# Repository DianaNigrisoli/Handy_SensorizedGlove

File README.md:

# Handy_SensorizedGlove
A wireless sensorized glove for ASL fingerspelling gesture recognition. 
### Course
Electronic Technologies and Biosensor Laboratories

### Developers 
- Arianna De Vecchi <br> arianna.devecchi@mail.polimi.it
- Ilaria Crupi <br> ilaria.crupi@mail.polimi.it
- Diana Nigrisoli <br> diana.nigrisoli@mail.polimi.it

### Setup
* In the command prompt execute:
    ```console
    git clone https://github.com/DianaNigrisoli/Handy_SensorizedGlove.git
    
### Development 
You can find all the scripts and designs in the following folders: 
* Hardware: EAGLE design of the PCB
* Firmware: PSoC Creator code
* Software: Python software for GUI development and Machine Learning classification 
* Box_Solidworks: SOLIDWORKS Part Document of the 3D printed box

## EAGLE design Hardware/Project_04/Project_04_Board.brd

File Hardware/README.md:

# Hardware

## Contents 
In "Project_04" folder: 

| File | Description |
|------|-------------|
| `Project_04_Schematic.sch` | Schematic |
| `Project_04_Board.brd` | Board |
| `Project_04_ToPrint.pdf` | PCB Design PDF file 1:1 scaled |
| `sparkfun.dru` | Design rules | 
| `README.md` | This README file. |

## Tools 

Both Schematic and Board Design were implemented using the 9.6.2 version of EAGLE software. 

## Detailed files description 
### Schematic 
#### List of schematic components 
| Name | Description | On PCB |
| --------- | ----------- | ------ |
| J1 | Plated through-hole 7 pin connector | Generic 0.1 inch spaced male headers connected to flex sensors and force-sensing resistors |
| J2 | Plated through-hole 7 pin connector | Generic 0.1 inch spaced male headers connected to 3.3V supply voltage | 
| J3.1 - PSOC | Plated through-hole 7 pin connector | Generic 0.1 inch spaced female headers connected to PSOC pins from 0.0 to 0.7 |
| J3.2 - PSOC | Plated through-hole 2 pin connector | Generic 0.1 inch spaced female headers connected to PSOC pins 12.0 (SCL) and 12.1 (SDA) |
| J3.3 - PSOC | Plated through-hole 4 pin connector | Generic 0.1 inch spaced female headers connected to PSOC pins 12.6 (RX), 12.7 (TX), 2.7 and 2.6 |
| J3.4 - PSOC | Plated through-hole 2 pin connector | Generic 0.1 inch spaced female headers connected to PSOC pins VDDIO and GND |
| J3 - LED | Plated through-hole 2 pin connector | Generic 0.1 inch spaced male headers connected to yellow LED |
| J4 - BATTERY | Plated through-hole 2 pin connector | Generic 0.1 inch spaced female headers connected to 4.5V external battery and external switch |
| J5 - BT | Plated through-hole 6 pin connector | Generic 0.1 inch spaced male headers connected to HC-05 Bluetooth module |
| J6 - ACC | Plated through-hole 6 pin connector | Generic 0.1 inch spaced male headers connected to LIS3DH Accelerometer |
| J7 - LDO | Plated through-hole 3 pin connector | Generic 0.1 inch spaced male headers connected to 3.3V voltage regulator |

### Board Design
55.88mm x 73.66 mm single layer board design according to the design rules in the sparkfun.dru file.

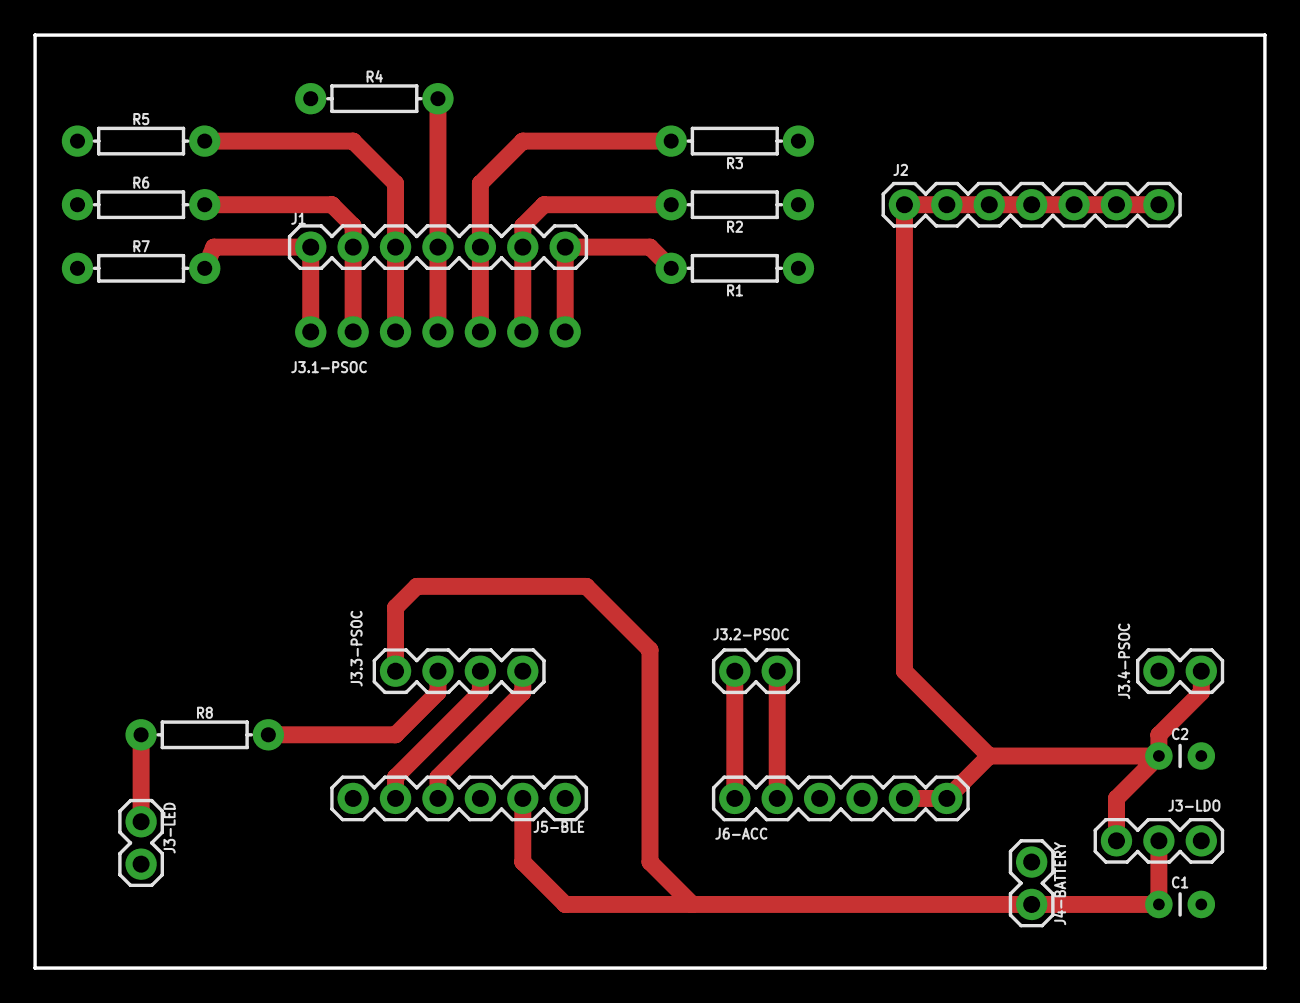
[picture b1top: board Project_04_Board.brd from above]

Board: 2 copper layers, 73.7 x 55.9 mm, 21 parts (1 on the bottom side), 15 nets.

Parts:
C1, C2: 1uF; CAP-PTH-2.54
J1, J2, J3.1-PSOC: 1X07
J3-LDO: 1X03
J3-LED, J3.2-PSOC, J3.4-PSOC, J4-BATTERY: 1X02
J3.3-PSOC: 1X04
J5-BLE, J6-ACC: 1X06
R1, R2, R3, R4, R5: 27K; AXIAL-0.3
R6, R7: 10K; AXIAL-0.3
R8: 330; AXIAL-0.3

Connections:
3.3V: C2.1, J2.1, J2.2, J2.3, J2.4, J2.5, J2.6, J2.7, J3-LDO.3, J3.4-PSOC.2, J6-ACC.5, J6-ACC.6
4.5V: C1.1, J3-LDO.2, J3.3-PSOC.1, J4-BATTERY.2, J5-BLE.2
GND: C1.2, C2.2, J3-LDO.1, J3-LED.2, J3.4-PSOC.1, J4-BATTERY.1, J5-BLE.3, J6-ACC.3, J6-ACC.4, R1.P$1, R2.P$1, R3.P$1, R4.P$1, R5.P$1, R6.P$1, R7.P$1
R1: J1.7, J3.1-PSOC.1, R1.P$2
R2: J1.6, J3.1-PSOC.2, R2.P$2
R3: J1.5, J3.1-PSOC.3, R3.P$2
R4: J1.4, J3.1-PSOC.4, R4.P$2
R5: J1.3, J3.1-PSOC.5, R5.P$2
R6: J1.2, J3.1-PSOC.6, R6.P$2
R7: J1.1, J3.1-PSOC.7, R7.P$2
RLED: J3-LED.1, J3.3-PSOC.2, R8.P$1, R8.P$2
RX: J3.3-PSOC.3, J5-BLE.5
SCL: J3.2-PSOC.2, J6-ACC.2
SDA: J3.2-PSOC.1, J6-ACC.1
TX: J3.3-PSOC.4, J5-BLE.4

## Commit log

2023-10-20 upload of final total project
2023-10-20 small change in power point

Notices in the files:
parts and their libraries:
SparkFun-Connectors: Licensing: Creative Commons ShareAlike 4.0 International - https://creativecommons.org/licenses/by-sa/4.0
